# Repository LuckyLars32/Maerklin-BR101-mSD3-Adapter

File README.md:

# Maerklin BR101 mSD3 Adapter
Adapterplatiene und Schallkapsel für den Einbau eines mSD3 Decoders + HLA in die Märklin BR101.  
Die Platine habe ich mit KiCAD Version 7.X erstellt.  
Die Schallkapsel habe ich mit einer 0.4er Düse, 0.2mm Layerhöhe und 50% Infill gedruckt.  

# Materialliste / BOM:
4x Widerstand 2,2 kΩ Bauform 0207 (der normale through-hole)  
1x 24 Pin Steckleiste (Push-Pull) gerade mit 1,27mm Raster  
1x Keramikkondensator 1206 (3216 metrisch) 1UF  
1x Märklin HLA Nachrüst Set 60941  
1x Märklin mSD3 oder anderer Sounddecoder mit NEM 660 Schnitstelle  
1x 15x11x3mm Lautsprecher 4-8 Ohm  

# Zusammenbau
Einbauseite immer wie Bedruckung auf der Platiene.
Die Wiederstände R1, R2, R3, R4 werden mit den 4x Widerstand 2,2 kΩ Bauform 0207 bestückt.
Die NEM660 Schnittstelle wird mit der 24 Pin Steckleiste mit 1,27mm Raster bestückt.
Der Keramikkondensator 1206 mit 1UF muss auf die Pads zwischen R1 und R3

# Pufferschaltung über mSD3 SUSI
Zusätzlich benötigte Komponenten:
2x Elko mit 500 - 1000 UF und max. 8,2 x 20 mm Radial
1x Schottkydiode mit 2 A Stromfestigkeit 25V Spannungsfestigkeit (mehr geht auch)
1x Widerstand 100 Ω
Zusammenbau:
Die beiden Elkos Paralell schalten. Dann die Scotty-Diode Parelell zum Wiederstand mit der + seite der Elkos verbinden.
Einbau:
Die Pufferschaltung dann mit +UB (+) und GND (-) auf der Adapterplatiene (bei eingebauter Platiene oben) verbinden.
Alternativ kann die Pufferschaltung auch an die Kontakte für den auf der Platiene integrierten Kondensator (bei eingebauter Platiene unten) angeschlossen werden. 
Diese Lötpads sind ebenso mit +UB und GND verbunden.

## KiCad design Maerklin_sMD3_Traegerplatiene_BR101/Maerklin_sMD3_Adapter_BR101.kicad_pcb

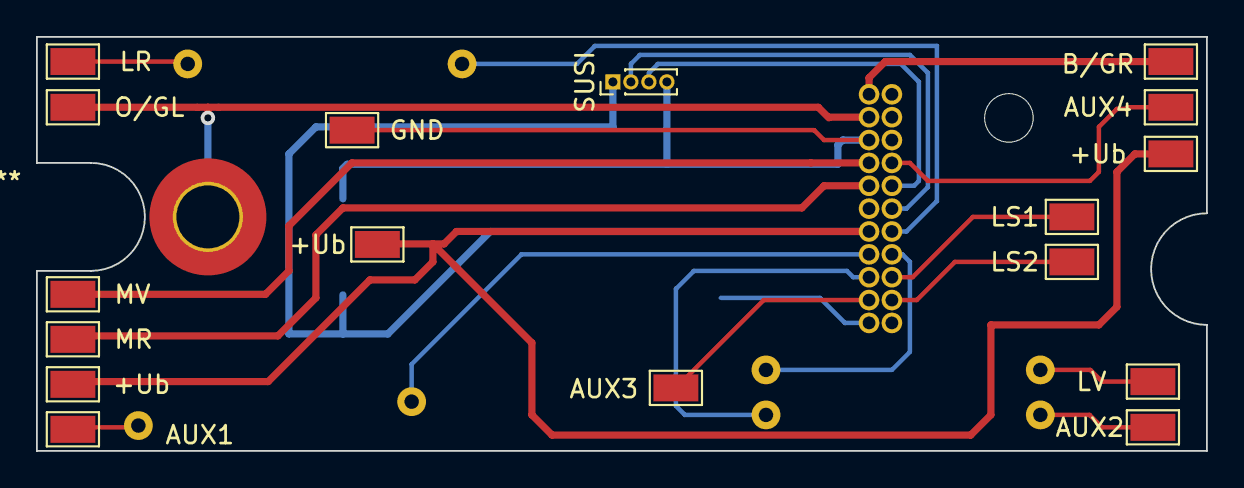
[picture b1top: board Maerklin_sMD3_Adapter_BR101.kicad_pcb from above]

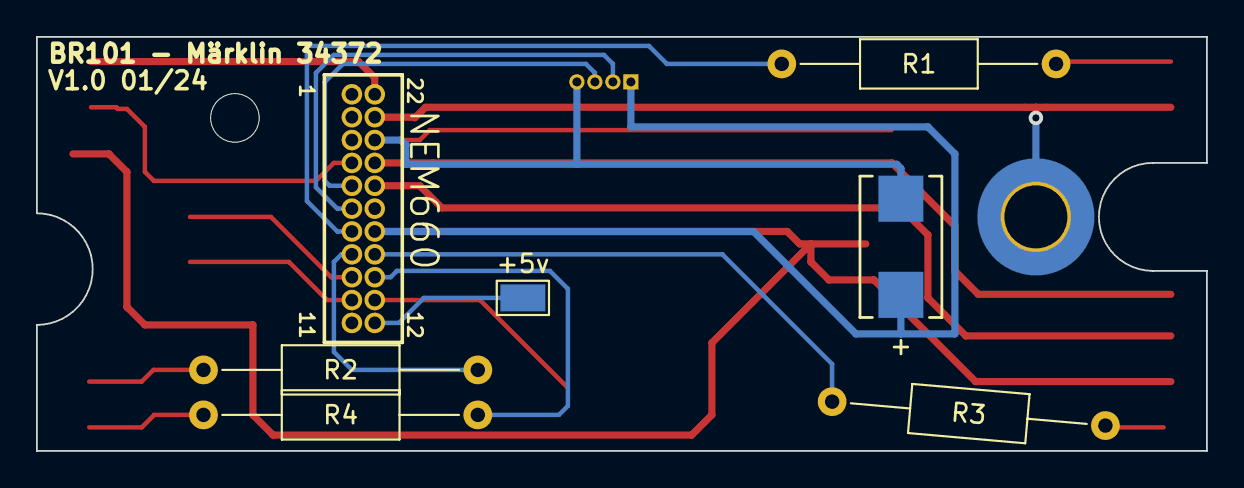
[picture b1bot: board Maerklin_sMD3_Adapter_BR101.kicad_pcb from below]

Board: 2 copper layers, 65.0 x 23.0 mm, 24 parts (7 on the bottom side), 21 nets.

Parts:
+5v: +5v; TestPoint_Pad_1.5x2.5mm
+Ub: +Ub; TestPoint_Pad_1.5x2.5mm
+Ub#2, +Ub#3: +Ub; TestPoint_Pad_1.5x2.5mm
AUX1: AUX1; TestPoint_Pad_1.5x2.5mm
AUX2: AUX2; TestPoint_Pad_1.5x2.5mm
AUX3: AUX3; TestPoint_Pad_1.5x2.5mm
AUX4: AUX4; TestPoint_Pad_1.5x2.5mm
B/GR: B/GR; TestPoint_Pad_1.5x2.5mm
C1: T491X108K006AT; CAPMP7.6X4.3_4.3N_KEM
GND: GND; TestPoint_Pad_1.5x2.5mm
LR: LR; TestPoint_Pad_1.5x2.5mm
LS1, LS2: LS; TestPoint_Pad_1.5x2.5mm
LV: LV; TestPoint_Pad_1.5x2.5mm
MR: MR; TestPoint_Pad_1.5x2.5mm
MV: MV; TestPoint_Pad_1.5x2.5mm
NEM660: SAMTEC-FTS-111-01-X-D
O/GL: O/GL; TestPoint_Pad_1.5x2.5mm
R1, R2, R3, R4: R_Axial_DIN0207_L6.3mm_D2.5mm_P15.24mm_Horizontal
SUSI: SUSI; PinHeader_1x04_P1.00mm_Vertical

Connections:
0/GL: NEM660.21, O/GL.1
+5v: +5v.1, NEM660.12
+Ub: +Ub.1, +Ub#2.1, +Ub#3.1, C1.1, NEM660.16, SUSI.1
AUX1: AUX1.1, R3.2
AUX2: AUX2.1, R4.2
AUX3: AUX3.1, NEM660.13
AUX4: AUX4.1, NEM660.4
B/GR: B/GR.1, NEM660.22
GND: C1.2, GND.1, NEM660.20, SUSI.4
LR: LR.1, R1.1
LS1: LS2.1, NEM660.10
LS2: LS1.1, NEM660.9
LV: LV.1, R2.1
MR: MR.1, NEM660.18
MV: MV.1, NEM660.19
unnamed: NEM660.7, R1.2
unnamed: NEM660.8, R2.2
unnamed: NEM660.14, R4.1
unnamed: NEM660.15, R3.1
SUSI2: NEM660.6, SUSI.2
SUSI3: NEM660.5, SUSI.3

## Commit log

2025-12-31 Initiale Version der README.md
2025-12-31 Pufferschaltung zu README.md hinzugefügt
2025-12-31 Bild von BR101 mSD3 Adapterplatiene
    Bild von BR101 mSD3 Adapterplatiene fertig Assembliert.
    Der Keramikkondensator ist hier nicht bestückt da bei nutzung der Pufferschaltung nicht zwingend nötig.
